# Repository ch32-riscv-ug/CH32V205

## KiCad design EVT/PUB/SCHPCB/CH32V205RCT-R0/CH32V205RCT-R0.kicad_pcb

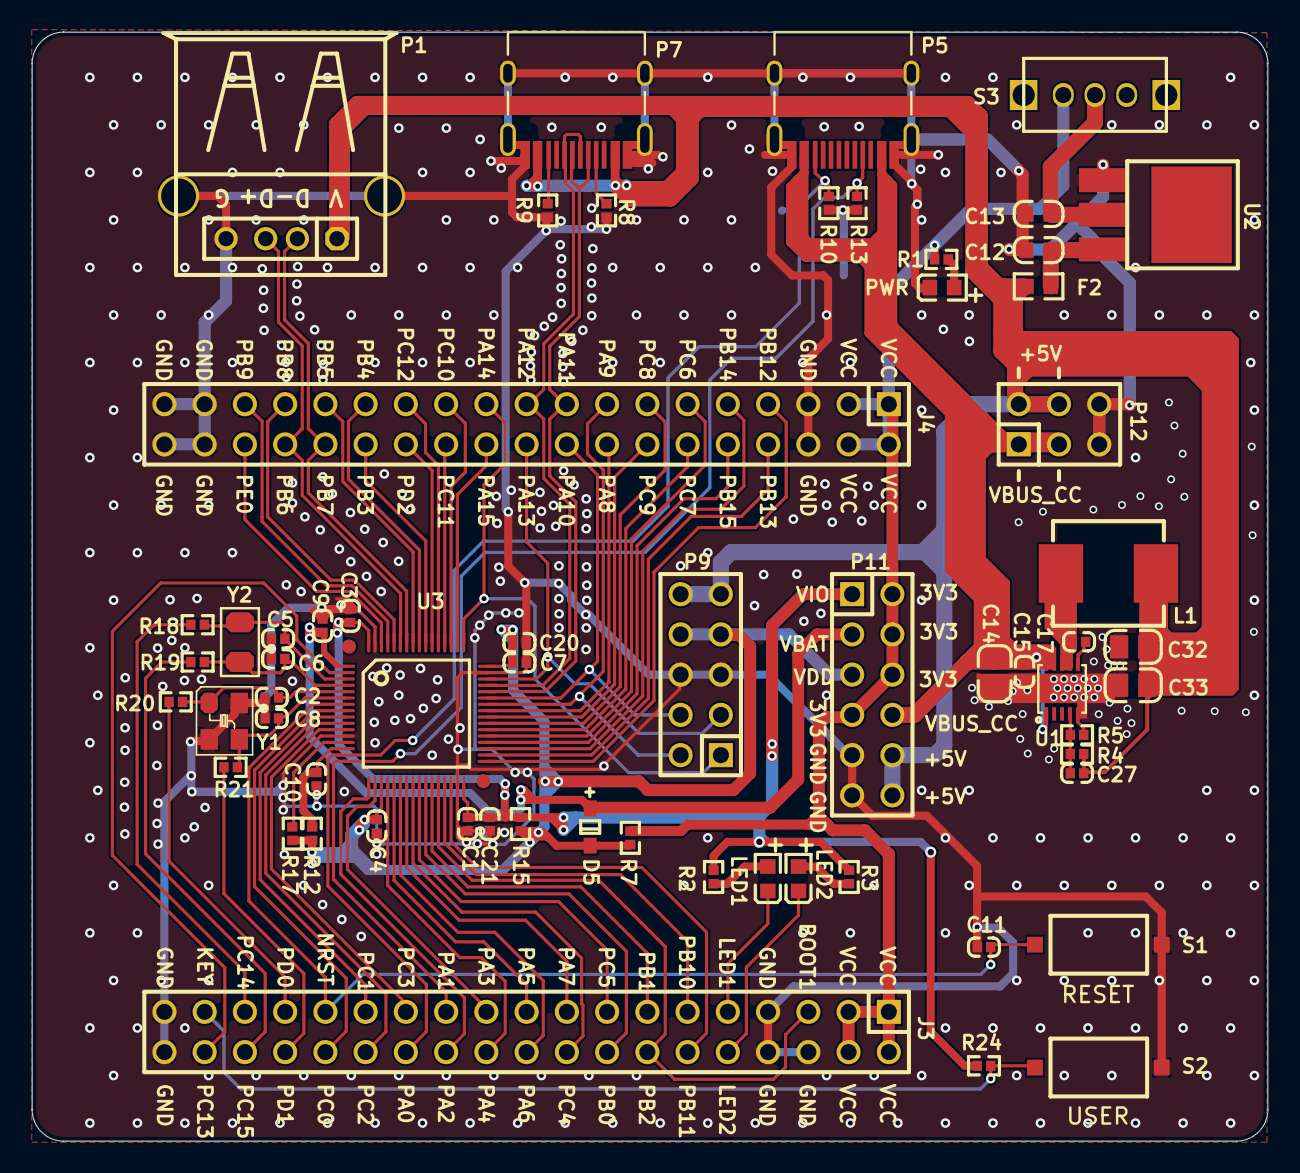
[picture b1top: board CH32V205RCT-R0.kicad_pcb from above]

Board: 2 copper layers, 78.0 x 70.0 mm, 61 parts (0 on the bottom side), 79 nets.

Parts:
C1, C3, C4, C7, C9, C10, C11: 0.1uF; 0402_C
C2, C8: 22pF; 0402_C
C5, C6: 12pF; 0402_C
C12, C13: 10uF; 0603_C
C14: NC(22uF/35V); 0805_C
C15: NC(0.1uF); 0402_C
C17: NC(100nF); 0402_C
C20, C21: 4.7uF; 0402_C
C27: NC(68pF); 0402_C
C32, C33: NC(22uF); 0805_C
D5: B0520WS; SOD-323
F2: 500mA; 0603
J3, J4: Header 19X2; IDC38-2.54mm
L1: NC(4.7uH/5A); IND-SMD_L7.0-W6.6
LED1: LED1 blue; 0603+
LED2: LED2 blue; 0603+
P1: USBHS; USBAF
P5: USBPD; TYPE-C-Receptacle-2.0
P7: TYPE-C; TYPE-C-Receptacle-2.0
P9: LINK; IDC10-2.54mm
P11: HEADER 6x2; IDC12-2.54mm
P12: HEADER 3x2; IDC6-2.54mm
PWR: POWER red; 0603+
R1, R2, R3: 1K; 0402
R4: NC(15K); 0402
R5: NC(4.7K); 0402
R7, R12, R15, R17: 0Ω; 0402
R8, R9, R10, R13: NC(5.1K); 0402
R18, R19, R20, R21: NC(0Ω); 0402
R24: 10K; 0402
S1: RESET; SMD_6.1x3.65x2.5mm-KEY
S2: USER; SMD_6.1x3.65x2.5mm-KEY
S3: SW; SW1
U1: NC(CH2024Q); DFN10_3X3
U2: 1117-3.3V; SOT-223
U3: CH32V205R; LQFP64_7X7
Y1: 8MHz; XT3225
Y2: 32.768k; FC-135

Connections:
3V3: J3.1, J3.2, J3.3, J3.4, J4.1, J4.2, J4.3, J4.4, P11.2, P11.4, P11.6, P11.7, R1.2, R7.1, S3.3
+5V: C27.1, C32.2, C33.2, F2.1, L1.2, P1.1, P7.A4, P7.B4, P9.9, P9.10, P11.10, P11.12, P12.2, P12.4, R4.2
BOOT1: J3.5, J3.14, U3.28
CC1: J3.26, P5.B5, R10.1, U3.15
CC2: J3.23, P5.A5, R13.1, U3.16
FB: C27.2, R4.1, R5.2, U1.4
GND: C1.1, C2.1, C3.1, C4.1, C5.2, C6.2, C7.1, C8.1, C9.2, C10.2, C11.1, C12.2, C13.2, C14.1, C15.1, C20.2, C21.1, C32.1, C33.1, J3.6, J3.7, J3.8, J3.37, J3.38, J4.5, J4.6, J4.35, J4.36, J4.37, J4.38, P1.0, P1.4, P5.0, P5.A1, P5.B1, P7.0, P7.A1, P7.B1, P9.5, P9.6, P11.9, P11.11, P12.5, P12.6, PWR.2, R5.1, R8.1, R9.1, R10.2, R13.2, S1.2, S2.2, U1.0, U1.5, U2.1, U3.12, U3.31, U3.47, U3.63, Y1.2, Y1.4
KEY: J3.35, R24.1, S2.1
LED1: J3.9, LED1.2
LED2: J3.10, LED2.2
NRST: C11.2, J3.29, S1.1, U3.7
NetC12_1: C12.1, F2.2, U2.3
NetC13_1: C13.1, S3.1, U2.2
NetC17_1: C17.1, U1.6
NetC17_2: C17.2, L1.1, U1.7, U1.8
NetLED1_1: LED1.1, R2.2
NetLED2_1: LED2.1, R3.2
NetP7_A5: P7.A5, R8.2
NetP7_B5: P7.B5, R9.2
NetPWR_1: PWR.1, R1.1
PA2: J3.24, U3.17
PA3: J3.21, U3.18
PA4: J3.22, U3.20
PA5: J3.19, U3.21
PA6: J3.20, U3.22
PA7: J3.17, U3.23
PA8: J4.16, U3.41
PA9: J4.15, P9.2, U3.42
PA10: J4.18, P9.4, U3.43
PA11: J4.17, P7.A7, P7.B7, U3.44
PA12: J4.19, P7.A6, P7.B6, U3.45
PA13: J4.20, P9.3, U3.46
PA14: J4.21, P9.1, U3.49
PA15: J4.22, U3.50
PB0: J3.16, U3.26
PB1: J3.13, U3.27
PB3: J4.28, U3.55
PB4: J4.27, U3.56
PB5: J4.29, U3.57
PB6: J4.32, P1.3, U3.59
PB7: J4.30, P1.2, U3.58
PB8: J4.31, U3.60
PB9: J4.33, U3.61
PB10: J3.11, U3.29
PB11: J3.12, U3.30
PB12: J4.7, U3.33
PB13: J4.8, U3.34
PB14: J4.9, U3.35
PB15: J4.10, U3.36
PC0: J3.30, U3.8
PC1: J3.27, U3.9
PC2: J3.28, U3.10
PC3: J3.25, U3.11
PC4: J3.18, U3.24
PC5: J3.15, U3.25
PC6: J4.11, U3.37
PC7: J4.12, U3.38
PC8: J4.13, U3.39
PC9: J4.14, U3.40
PC10: J4.23, U3.51
PC11: J4.24, U3.52
PC12: J4.25, U3.53
PC13: J3.36, U3.2
PC14: J3.33, R18.2
PC15: J3.34, R19.1
PD0: J3.31, R20.1
PD1: J3.32, R21.1
PD2: J4.26, U3.54
PE0: J4.34, U3.62
VBAT: C9.1, D5.1, P11.3, U3.1
VBUS_CC: C14.2, C15.2, P5.A4, P5.B4, P11.8, P12.1, P12.3, U1.1, U1.9, U1.10
VDD: C4.2, C7.2, C20.1, D5.2, P9.7, P9.8, P11.5, R7.2, R12.2, R15.2, R17.1, U3.19, U3.48
VDDA: C10.1, R12.1, U3.14
VIO: C1.2, C3.2, C21.2, P11.1, R2.1, R3.1, R15.1, R24.2, U3.32, U3.64
VREF+: R17.2, U3.13
X32KI: C5.1, R18.1, U3.3, Y2.1
X32KO: C6.1, R19.2, U3.4, Y2.2
XI: C2.2, R20.2, U3.5, Y1.1
XO: C8.2, R21.2, U3.6, Y1.3

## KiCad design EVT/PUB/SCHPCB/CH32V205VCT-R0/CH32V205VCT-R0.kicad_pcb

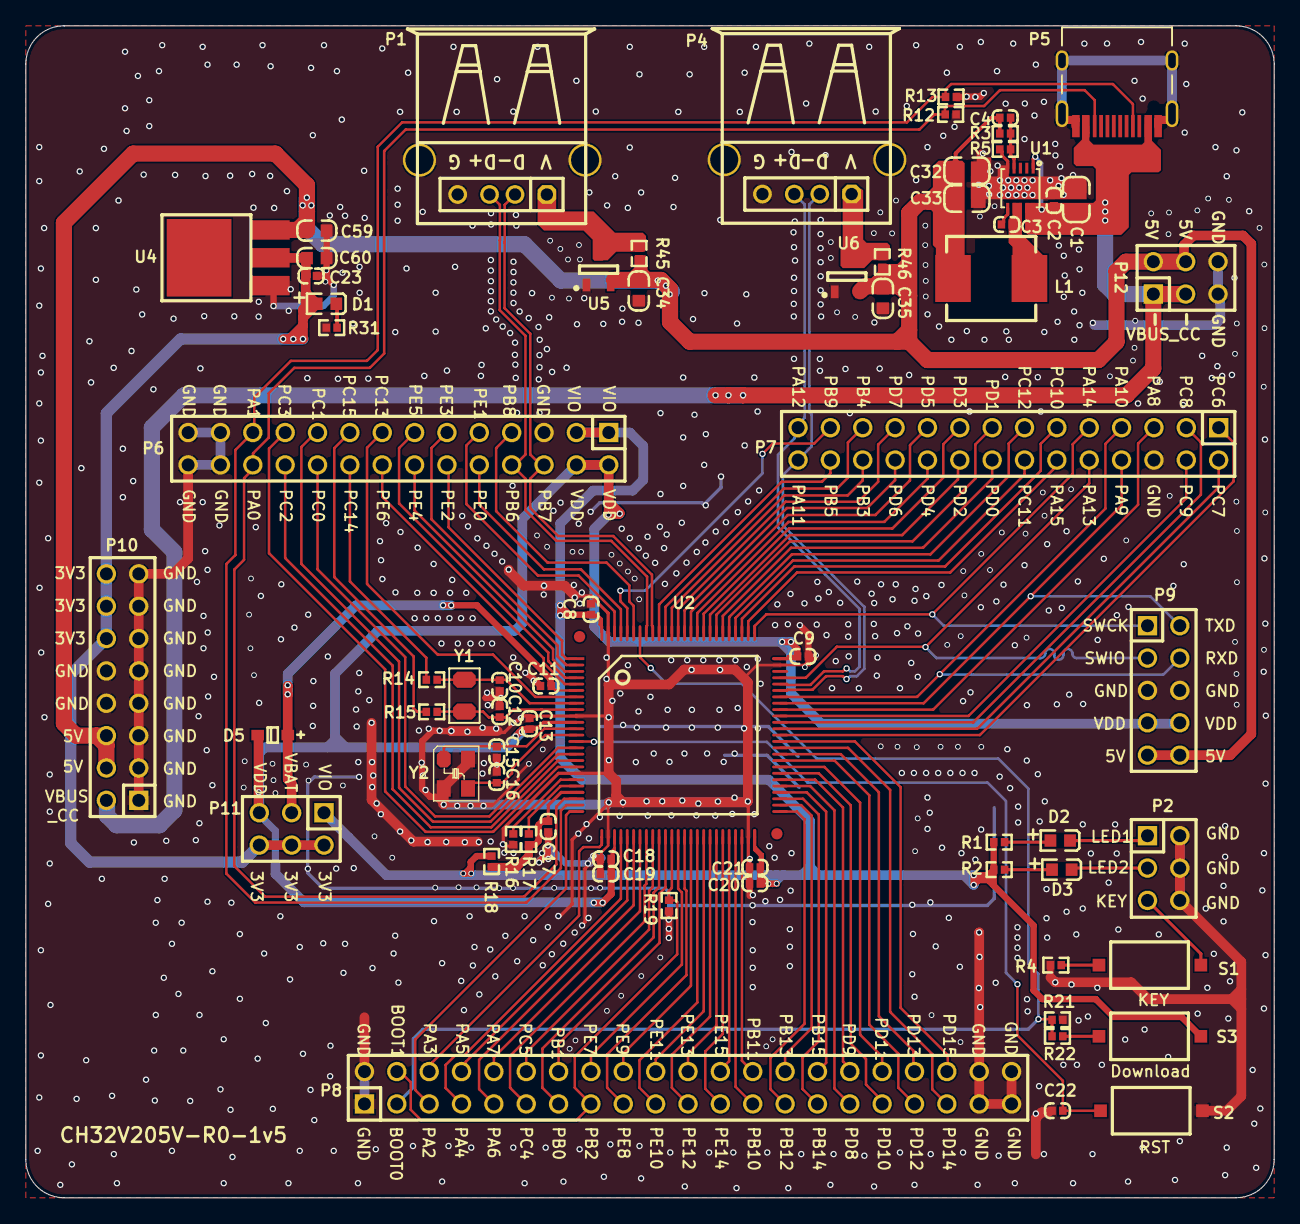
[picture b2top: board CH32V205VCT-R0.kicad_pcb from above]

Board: 2 copper layers, 98.0 x 92.0 mm, 69 parts (0 on the bottom side), 109 nets.

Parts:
C1: NC(22uF/35V); 0805_C
C2: NC(0.1uF); 0402_C
C3: NC(100nF); 0402_C
C4: NC(68pF); 0402_C
C8, C9, C11, C13, C17, C18, C21, C22, C23: 0.1uF; 0402_C
C10, C12: 12pF; 0402_C
C15, C16: 22pF; 0402_C
C19, C20: 4.7uF; 0402_C
C32, C33: NC(22uF); 0805_C
C34, C35, C59, C60: 10uF; 0603_C
D1, D3: RED; 0603+
D2: BLUE; 0603+
D5: B0520WS; SOD-323
L1: NC(4.7uH/5A); IND-SMD_L7.0-W6.6
P1: USBHS; USBAF
P2: IO; IDC6-2.54mm
P4: USBFS; USBAF
P5: USBPD; TYPE-C-Receptacle-2.0
P6, P7: IDC28-2.54MM
P8: HEADER 21x2; IDC42-2.54MM
P9: LINK; IDC10-2.54mm
P10: HEADER 8x2; IDC16-2.54mm
P11, P12: HEADER 3x2; IDC6-2.54mm
R1, R2, R22, R31: 1K; 0402
R3: NC(15K); 0402
R4, R19, R21: 10K; 0402
R5: NC(4.7K); 0402
R12, R13: NC(5.1K); 0402
R14, R15: NC(0R); 0402
R16, R17, R18: 0R; 0402
R45, R46: NC(0Ω); 0402
S1: KEY; SMD_6.1x3.65x2.5mm-KEY
S2: RST#; SMD_6.1x3.65x2.5mm-KEY
S3: Download; SMD_6.1x3.65x2.5mm-KEY
U1: NC(CH2024Q); DFN10_3X3
U2: CH32V205V; LQFP100
U4: 1117-3.3V; SOT-223
U5, U6: CH213; SOT-23-3
Y1: 32768Hz; FC-135
Y2: 8MHz; XT3225

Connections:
3V3: C23.1, C60.1, D1.1, P10.12, P10.14, P10.16, P11.2, P11.4, P11.6, U4.2
5V: C4.1, C32.2, C33.2, C34.1, C35.1, C59.1, L1.2, P9.9, P9.10, P10.4, P10.6, P12.2, P12.4, R3.2, R45.1, R46.1, U4.3, U5.2, U6.2
BOOT0: P8.3, R21.1, R22.1, U2.94
BOOT1: P8.4, P8.15, R19.1, U2.37
CC1: P5.B5, P6.24, R12.1, U2.23
CC2: P5.A5, P6.23, R13.1, U2.24
FB: C4.2, R3.1, R5.2, U1.4
GND: C1.1, C2.1, C8.1, C9.2, C10.1, C11.1, C12.1, C13.2, C15.1, C16.1, C17.2, C18.1, C19.2, C20.2, C21.2, C22.1, C23.2, C32.1, C33.1, C34.2, C35.2, C59.2, C60.2, P1.0, P1.4, P2.2, P2.4, P2.6, P4.0, P4.4, P5.0, P5.A1, P5.B1, P6.5, P6.25, P6.26, P6.27, P6.28, P7.6, P8.1, P8.2, P8.39, P8.40, P8.41, P8.42, P9.5, P9.6, P10.1, P10.3, P10.5, P10.7, P10.8, P10.9, P10.10, P10.11, P10.13, P10.15, P12.5, P12.6, R4.1, R5.1, R12.2, R13.2, R16.1, R19.2, R21.2, R31.1, S2.1, U1.0, U1.5, U2.10, U2.19, U2.27, U2.49, U2.74, U2.99, U4.1, U5.1, U6.1, Y2.2, Y2.4
KEY: P2.5, S1.1
LED1: D2.2, P2.1
LED2: D3.2, P2.3
NRST: C22.2, S2.2, U2.14
NetC3_1: C3.1, U1.6
NetC3_2: C3.2, L1.1, U1.7, U1.8
NetD1_2: D1.2, R31.2
NetD2_1: D2.1, R1.2
NetD3_1: D3.1, R2.2
NetR4_2: R4.2, S1.2
NetR22_2: R22.2, S3.2
PA2: P8.5, U2.25
PA3: P8.6, U2.26
PA4: P8.7, U2.29
PA5: P8.8, U2.30
PA6: P8.9, U2.31
PA7: P8.10, U2.32
PA8: P7.5, U2.67
PA9: P7.8, P9.2, U2.68
PA10: P7.7, P9.4, U2.69
PA11: P4.2, P7.28, U2.70
PA12: P4.3, P7.27, U2.71
PA13: P7.10, P9.3, U2.72
PA14: P7.9, P9.1, U2.76
PA15: P7.12, U2.77
PB0: P8.13, U2.35
PB1: P8.14, U2.36
PB3: P7.24, U2.89
PB4: P7.23, U2.90
PB5: P7.26, U2.91
PB6: P1.3, P6.8, U2.93
PB7: P1.2, P6.6, U2.92
PB8: P6.7, U2.95
PB9: P7.25, U2.96
PB10: P8.25, U2.47
PB11: P8.26, U2.48
PB12: P8.27, U2.51
PB13: P8.28, U2.52
PB14: P8.29, U2.53
PB15: P8.30, U2.54
PC0: P6.20, U2.15
PC1: P6.19, U2.16
PC2: P6.22, U2.17
PC3: P6.21, U2.18
PC4: P8.11, U2.33
PC5: P8.12, U2.34
PC6: P7.1, U2.63
PC7: P7.2, U2.64
PC8: P7.3, U2.65
PC9: P7.4, U2.66
PC10: P7.11, U2.78
PC11: P7.14, U2.79
PC12: P7.13, U2.80
PC13: P6.15, U2.7
PC14: P6.18, R14.1
PC15: P6.17, R15.1
PD0: P7.16, U2.81
PD1: P7.15, U2.82
PD2: P7.18, U2.83
PD3: P7.17, U2.84
PD4: P7.20, U2.85
PD5: P7.19, U2.86
PD6: P7.22, U2.87
PD7: P7.21, U2.88
PD8: P8.31, U2.55
PD9: P8.32, U2.56
PD10: P8.33, U2.57
PD11: P8.34, U2.58
PD12: P8.35, U2.59
PD13: P8.36, U2.60
PD14: P8.37, U2.61
PD15: P8.38, U2.62
PE0: P6.10, U2.97
PE1: P6.9, U2.98
PE2: P6.12, U2.1
PE3: P6.11, U2.2
PE4: P6.14, U2.3
PE5: P6.13, U2.4
PE6: P6.16, U2.5
PE7: P8.16, U2.38
PE8: P8.17, U2.39
PE9: P8.18, U2.40
PE10: P8.19, U2.41
PE11: P8.20, U2.42
PE12: P8.21, U2.43
PE13: P8.22, U2.44
PE14: P8.23, U2.45
PE15: P8.24, U2.46
VBAT: C11.2, D5.1, P11.3, U2.6
VBUS_CC: C1.2, C2.2, P5.A4, P5.B4, P10.2, P12.1, P12.3, U1.1, U1.9, U1.10
VBUS_FS: P4.1, R46.2, U6.3
VBUS_HS: P1.1, R45.2, U5.3
VDD: C9.1, C13.1, C18.2, C19.1, D5.2, P6.2, P6.4, P9.7, P9.8, P11.5, U2.11, U2.28, U2.75
VDDA: C17.1, R17.1, R18.2, U2.22
VIO: C8.2, C20.1, C21.1, P6.1, P6.3, P11.1, R1.1, R2.1, R18.1, S3.1, U2.50, U2.100
VREF+: R17.2, U2.21
VREF-: R16.2, U2.20
X32KI: C10.2, R14.2, U2.8, Y1.1
X32KO: C12.2, R15.2, U2.9, Y1.2
XI: C15.2, U2.12, Y2.1
XO: C16.2, U2.13, Y2.3

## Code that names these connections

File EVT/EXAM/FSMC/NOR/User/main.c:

/********************************** (C) COPYRIGHT *******************************
 * File Name          : main.c
 * Author             : WCH
 * Version            : V1.0.1
 * Date               : 2026/10/14
 * Description        : Main program body.
 *********************************************************************************
 * Copyright (c) 2021 Nanjing Qinheng Microelectronics Co., Ltd.
 * Attention: This software (modified or not) and binary are used for 
 * microcontroller manufactured by Nanjing Qinheng Microelectronics.
 *******************************************************************************/

/*
 *@Note
   This example is used to demonstrate the FSMC interface operating NorFlash-MT28EW128ABA1LJS-0SIT.
  PIN:
   (Latches)
    FSMC_NADV     -    PB7
    FSMC_NOE      -    PD4  (OE)
    FSMC_NWE      -    PD5  (WE)
    FSMC_NWAIT    -    PD6  (RY/BY#)
    FSMC_NE1      -    PD7  (CE)
    FSMC_D/A0     -    PD14
    FSMC_D/A1     -    PD15
    FSMC_D/A2     -    PD0
    FSMC_D/A3     -    PD1
    FSMC_D/A4     -    PE7
    FSMC_D/A5     -    PE8
    FSMC_D/A6     -    PE9
    FSMC_D/A7     -    PE10
    FSMC_D/A8     -    PE11
    FSMC_D/A9     -    PE12
    FSMC_D/A10    -    PE13
    FSMC_D/A11    -    PE14
    FSMC_D/A12    -    PE15
    FSMC_D/A13    -    PD8
    FSMC_D/A14    -    PD9
    FSMC_D/A15    -    PD10
    FSMC_A16      -    PD11
    FSMC_A17      -    PD12
    FSMC_A18      -    PD13
    FSMC_A19      -    PE3
    FSMC_A20      -    PE4
    FSMC_A21      -    PE5
    FSMC_A22      -    PE6

  The address line and data line of this routine are multiplexed
  and need to use a latch.
*/

#include "debug.h"
#include "FSMC_NOR.h"
/* Global define */
uint16_t TxBuffer[BUFFER_SIZE];
uint16_t RxBuffer[BUFFER_SIZE];
uint32_t WriteReadStatus = 0, Index = 0;
NOR_IDTypeDef NOR_ID;
/* Global Variable */


/*********************************************************************
 * @fn      main
 *
 * @brief   Main program.
 *
 * @return  none
 */
int main(void)
{
    SystemCoreClockUpdate();
    Delay_Init();
    USART_Printf_Init(115200);
    printf ("SystemCoreClk:%lu\r\n", (unsigned long)SystemCoreClock);
    printf("ChipID:%08x\r\n", DBGMCU_GetCHIPID() );
    printf("NorFlash TEST\n");

    FSMC_NorFlash_Init();
    NOR_ReadID(&NOR_ID);
    NOR_ReturnToReadMode();
    NOR_EraseBlock(WRITE_READ_ADDR);
    Fill_Buffer(TxBuffer, BUFFER_SIZE, 0x01);
    NOR_WriteBuffer(TxBuffer, WRITE_READ_ADDR, BUFFER_SIZE);
    NOR_ReadBuffer(RxBuffer, WRITE_READ_ADDR, BUFFER_SIZE);
    for (Index = 0x00; (Index < BUFFER_SIZE) && (WriteReadStatus == 0); Index++)
    {
        if (RxBuffer[Index] != TxBuffer[Index])
        {
            WriteReadStatus = Index + 1;
            printf("RxBuffer[%d]=%x\r\n",Index,RxBuffer[Index]);
            printf("TxBuffer[%d]=%x\r\n",Index,TxBuffer[Index]);
        }
    }
    if (WriteReadStatus == 0)
    {
        /* OK */
        printf("sucess\r\n");
    }
    else
    {
        /* KO */
        printf("error\r\n");
    }
    while(1);
}

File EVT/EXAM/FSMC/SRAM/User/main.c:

/********************************** (C) COPYRIGHT *******************************
 * File Name          : main.c
 * Author             : WCH
 * Version            : V1.0.1
 * Date               : 2026/10/14
 * Description        : Main program body.
 *********************************************************************************
 * Copyright (c) 2021 Nanjing Qinheng Microelectronics Co., Ltd.
 * Attention: This software (modified or not) and binary are used for 
 * microcontroller manufactured by Nanjing Qinheng Microelectronics.
 *******************************************************************************/

/*
 *@Note
   FSMC routine to operate NOR_ SRAM:
      This routine demonstrates the operation of IS62WV25616BLL model
      NOR_SRAM erase-read through FSMC interface.
  PIN:
    FSMC_NADV   -    PB7
    FSMC_NE1    -    PD7 (CS1)
    FSMC_NOE    -    PD4  (OE)
    FSMC_NWE    -    PD5  (WE)
    FSMC_NBL1   -    PE1  (UB)
    FSMC_NBL0   -    PE0  (LB)
    FSMC_D0     -    PD14
    FSMC_D1     -    PD15
    FSMC_D2     -    PD0
    FSMC_D3     -    PD1
    FSMC_D4     -    PE7
    FSMC_D5     -    PE8
    FSMC_D6     -    PE9
    FSMC_D7     -    PE10
    FSMC_D8     -    PE11
    FSMC_D9     -    PE12
    FSMC_D10    -    PE13
    FSMC_D11    -    PE14
    FSMC_D12    -    PE15
    FSMC_D13    -    PD8
    FSMC_D14    -    PD9
    FSMC_D15    -    PD10
    FSMC_A16    -    PD11
    FSMC_A17    -    PD12

  The address line and data line of this routine are multiplexed
  and need to use a latch.
*/

#include "debug.h"

/* Global define */
#define Bank1_SRAM1_ADDR    ((u32)(0x60000000))
/* Global Variable */
/*********************************************************************
 * @fn      FSMC_SRAM_Init
 *
 * @brief   Init FSMC
 *
 * @return  none
 */
void FSMC_SRAM_Init(void)
{
    FSMC_NORSRAMInitTypeDef  FSMC_NORSRAMInitStructure={0};
    FSMC_NORSRAMTimingInitTypeDef  readWriteTiming={0};
    GPIO_InitTypeDef  GPIO_InitStructure={0};

    RCC_PB2PeriphClockCmd(RCC_PB2Periph_GPIOB | RCC_PB2Periph_GPIOD | RCC_PB2Periph_GPIOE|RCC_PB2Periph_AFIO,ENABLE);
    RCC_HBPeriphClockCmd(RCC_HBPeriph_FSMC,ENABLE);
    /* FSMC_NADV */
    GPIO_InitStructure.GPIO_Pin = GPIO_Pin_7;
    GPIO_InitStructure.GPIO_Mode = GPIO_Mode_AF_PP;
    GPIO_InitStructure.GPIO_Speed = GPIO_Speed_High;
    GPIO_Init(GPIOB, &GPIO_InitStructure);
    GPIO_PinAFConfig(GPIOB, GPIO_PinSource7, GPIO_AF6);

    GPIO_InitStructure.GPIO_Pin = GPIO_Pin_0|GPIO_Pin_1|GPIO_Pin_4|GPIO_Pin_5|GPIO_Pin_7|GPIO_Pin_8|GPIO_Pin_9|GPIO_Pin_10|GPIO_Pin_11|GPIO_Pin_12|GPIO_Pin_14|GPIO_Pin_15;
    GPIO_InitStructure.GPIO_Mode = GPIO_Mode_AF_PP;
    GPIO_InitStructure.GPIO_Speed = GPIO_Speed_High;
    GPIO_Init(GPIOD, &GPIO_InitStructure);
    GPIO_PinAFConfig(GPIOD, GPIO_PinSource0, GPIO_AF7);
    GPIO_PinAFConfig(GPIOD, GPIO_PinSource1, GPIO_AF7);
    GPIO_PinAFConfig(GPIOD, GPIO_PinSource4, GPIO_AF7);
    GPIO_PinAFConfig(GPIOD, GPIO_PinSource5, GPIO_AF7);   
    GPIO_PinAFConfig(GPIOD, GPIO_PinSource7, GPIO_AF7); 
    GPIO_PinAFConfig(GPIOD, GPIO_PinSource8, GPIO_AF7);
    GPIO_PinAFConfig(GPIOD, GPIO_PinSource9, GPIO_AF7);
    GPIO_PinAFConfig(GPIOD, GPIO_PinSource10, GPIO_AF7);
    GPIO_PinAFConfig(GPIOD, GPIO_PinSource11, GPIO_AF7);
    GPIO_PinAFConfig(GPIOD, GPIO_PinSource12, GPIO_AF7);
    GPIO_PinAFConfig(GPIOD, GPIO_PinSource14, GPIO_AF7);
    GPIO_PinAFConfig(GPIOD, GPIO_PinSource15, GPIO_AF7);

    GPIO_InitStructure.GPIO_Pin = GPIO_Pin_0|GPIO_Pin_1|GPIO_Pin_7|GPIO_Pin_8|GPIO_Pin_9|GPIO_Pin_10|GPIO_Pin_11|GPIO_Pin_12|GPIO_Pin_13|GPIO_Pin_14|GPIO_Pin_15;
    GPIO_InitStructure.GPIO_Mode = GPIO_Mode_AF_PP;
    GPIO_InitStructure.GPIO_Speed = GPIO_Speed_High;
    GPIO_Init(GPIOE, &GPIO_InitStructure);
    GPIO_PinAFConfig(GPIOE, GPIO_PinSource0, GPIO_AF7);
    GPIO_PinAFConfig(GPIOE, GPIO_PinSource1, GPIO_AF7);
    GPIO_PinAFConfig(GPIOE, GPIO_PinSource7, GPIO_AF7);
    GPIO_PinAFConfig(GPIOE, GPIO_PinSource8, GPIO_AF7);
    GPIO_PinAFConfig(GPIOE, GPIO_PinSource9, GPIO_AF7);
    GPIO_PinAFConfig(GPIOE, GPIO_PinSource10, GPIO_AF7);
    GPIO_PinAFConfig(GPIOE, GPIO_PinSource11, GPIO_AF7);
    GPIO_PinAFConfig(GPIOE, GPIO_PinSource12, GPIO_AF7);
    GPIO_PinAFConfig(GPIOE, GPIO_PinSource13, GPIO_AF7);
    GPIO_PinAFConfig(GPIOE, GPIO_PinSource14, GPIO_AF7);
    GPIO_PinAFConfig(GPIOE, GPIO_PinSource15, GPIO_AF7);

    readWriteTiming.FSMC_AddressSetupTime = 0x00;
    readWriteTiming.FSMC_AddressHoldTime = 0x00;
    readWriteTiming.FSMC_DataSetupTime = 0x03;
    readWriteTiming.FSMC_BusTurnAroundDuration = 0x00;
    readWriteTiming.FSMC_AccessMode = FSMC_AccessMode_A;

    FSMC_NORSRAMInitStructure.FSMC_Bank = FSMC_Bank1_NORSRAM1;
    FSMC_NORSRAMInitStructure.FSMC_DataAddressMux = FSMC_DataAddressMux_Enable;
    FSMC_NORSRAMInitStructure.FSMC_MemoryType =FSMC_MemoryType_SRAM;
    FSMC_NORSRAMInitStructure.FSMC_MemoryDataWidth = FSMC_MemoryDataWidth_16b;
    FSMC_NORSRAMInitStructure.FSMC_BurstAccessMode =FSMC_BurstAccessMode_Disable;
    FSMC_NORSRAMInitStructure.FSMC_WaitSignalPolarity = FSMC_WaitSignalPolarity_Low;
    FSMC_NORSRAMInitStructure.FSMC_AsynchronousWait=FSMC_AsynchronousWait_Disable;
    FSMC_NORSRAMInitStructure.FSMC_WaitSignalActive = FSMC_WaitSignalActive_BeforeWaitState;
    FSMC_NORSRAMInitStructure.FSMC_WriteOperation = FSMC_WriteOperation_Enable;
    FSMC_NORSRAMInitStructure.FSMC_WaitSignal = FSMC_WaitSignal_Disable;
    FSMC_NORSRAMInitStructure.FSMC_ExtendedMode = FSMC_ExtendedMode_Disable;
    FSMC_NORSRAMInitStructure.FSMC_WriteBurst = FSMC_WriteBurst_Disable;
    FSMC_NORSRAMInitStructure.FSMC_ReadWriteTimingStruct = &readWriteTiming;
    FSMC_NORSRAMInitStructure.FSMC_WriteTimingStruct = &readWriteTiming;

    FSMC_NORSRAMInit(&FSMC_NORSRAMInitStructure);
    FSMC_NORSRAMCmd(FSMC_Bank1_NORSRAM1, ENABLE);
}



/*********************************************************************
 * @fn      main
 *
 * @brief   Main program.
 *
 * @return  none
 */
int main(void)
{
    u32 i=0;
    SystemCoreClockUpdate();
    Delay_Init();
    USART_Printf_Init(115200);
    printf ("SystemCoreClk:%lu\r\n", (unsigned long)SystemCoreClock);
    printf("ChipID:%08x\r\n", DBGMCU_GetCHIPID() );
    printf("SRAM TEST\r\n");

	FSMC_SRAM_Init();

	printf("Write data:\n");
	for(i=0; i<1024; i++){
      *(u32*)(Bank1_SRAM1_ADDR + 4*i) = i;
	}

	printf("Read data:\n");
	for(i=0; i<1024; i++){
      printf("%08x ", *(u32*)(Bank1_SRAM1_ADDR + 4*i));
    } printf("\n");

	while(1);
}

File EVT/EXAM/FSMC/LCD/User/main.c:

/********************************** (C) COPYRIGHT *******************************
 * File Name          : main.c
 * Author             : WCH
 * Version            : V1.0.1
 * Date               : 2026/10/14
 * Description        : Main program body.
 *********************************************************************************
 * Copyright (c) 2021 Nanjing Qinheng Microelectronics Co., Ltd.
 * Attention: This software (modified or not) and binary are used for 
 * microcontroller manufactured by Nanjing Qinheng Microelectronics.
 *******************************************************************************/

/*
 *@Note
   FSMC routine to operate TFTLCD:
  LCD--PIN:
    PD11--FSMC_A16
    PD12--FSMC_A17
    PD5 --FSMC_NEW
    PD4 --FSMC_NOE
    PA15--LCDRST#
    PD14--FSMC_D0
    PD15--FSMC_D1
    PD0 --FSMC_D2
    PD1--FSMC_D3
    PE7--FSMC_D4
    PE8 --FSMC_D5
    PE9 --FSMC_D6
    PE10--FSMC_D7
    PE11--FSMC_D8
    PE12--FSMC_D9
    PE13--FSMC_D10
    PE14--FSMC_D11
    PE15--FSMC_D12
    PD8 --FSMC_D13
    PD9--FSMC_D14
    PD10--FSMC_D15
    PB14--IO_BLCTR
*/


#include "debug.h"
#include "lcd.h"
/* Global define */

/* Global Variable */

/*********************************************************************
 * @fn      LCD_Reset_GPIO_Init
 *
 * @brief   Init LCD reset GPIO.
 *
 * @return  none
 */
void LCD_Reset_GPIO_Init(void)
{
    GPIO_InitTypeDef  GPIO_InitStructure={0};

    RCC_PB2PeriphClockCmd(RCC_PB2Periph_GPIOA, ENABLE);
    GPIO_InitStructure.GPIO_Pin = GPIO_Pin_15;
    GPIO_InitStructure.GPIO_Mode = GPIO_Mode_Out_PP;
    GPIO_InitStructure.GPIO_Speed = GPIO_Speed_High;
    GPIO_Init(GPIOA, &GPIO_InitStructure);
    GPIO_SetBits(GPIOA,GPIO_Pin_15);
}


/*********************************************************************
 * @fn      main
 *
 * @brief   Main program.
 *
 * @return  none
 */
int main(void)
{
	u8 x=0;
	LCD_Reset_GPIO_Init();
	//LCD reset
	GPIO_ResetBits(GPIOA,GPIO_Pin_15);
	Delay_Ms(100);
	GPIO_SetBits(GPIOA,GPIO_Pin_15);

    LCD_Init();
	POINT_COLOR=RED;		
	 
    while(1) 
	{		 
		switch(x)
		{
			case 0:LCD_Clear(WHITE);break;
			case 1:LCD_Clear(BLACK);break;
			case 2:LCD_Clear(BLUE);break;
			case 3:LCD_Clear(RED);break;
			case 4:LCD_Clear(MAGENTA);break;
			case 5:LCD_Clear(GREEN);break;
			case 6:LCD_Clear(CYAN);break;
			case 7:LCD_Clear(YELLOW);break;
			case 8:LCD_Clear(BRRED);break;
			case 9:LCD_Clear(GRAY);break;
			case 10:LCD_Clear(LGRAY);break;
			case 11:LCD_Clear(BROWN);break;
            default:break;
		}
		POINT_COLOR=RED;	  
		LCD_ShowString(30,40,210,24,24,"CH32V205");
        Delay_Ms(5);
		LCD_ShowString(30,70,200,16,16,"TFTLCD TEST");
        Delay_Ms(5);
		LCD_ShowString(30,90,200,16,16,"WCH");
        Delay_Ms(5);
	    x++;
		if(x==12)x=0;			   		 
		Delay_Ms(1000);	

	} 
}

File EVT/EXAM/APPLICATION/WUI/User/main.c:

/********************************** (C) COPYRIGHT *******************************
 * File Name          : main.c
 * Author             : WCH
 * Version            : V1.0.0
 * Date               : 2026/08/12
 * Description        : Main program body.
 *********************************************************************************
 * Copyright (c) 2023 Nanjing Qinheng Microelectronics Co., Ltd.
 * Attention: This software (modified or not) and binary are used for
 * microcontroller manufactured by Nanjing Qinheng Microelectronics.
 *******************************************************************************/

/*
 *@Note
 A demo for wui
  pins: 
    FLASH_CS   -- PA4
    FLASH_DO   -- PA6
    FLASH_DI   -- PA7
    FLASH_CLK  -- PA5
    
    QSPI_SCK   -- PB2
    QSPI_SIOX0 -- PB8
    LCD_RST    -- PC13
    QSPI_SIOX1 -- PB9
    QSPI_CSX   -- PB1
    BL_EN      -- PB3
    QSPI_SIOX2 -- PB10
    QSPI_SIOX3 -- PB11
    IIC_SDA    -- PB7
    IIC_SCL    -- PB6
    TR_RST     -- PB14
    TR_INT     -- PB15
 */

#include "debug.h"
#include "string.h"
#include "ch32v205_qspi.h"
#include "wui.h"
#include "wui_user/wui_page.h"
#include "touch.h"
#include "wui_port.h"
/* Global define */

/* Global Variable */

static uint8_t wui_heap_buffer[4 * 1024];
#define TIM_PCK (8000ul)
// WUIconfig init
static const wui_init_data_t wui_init_data = {
    .page_count = WUI_PAGE_COUNT,
    .width = LCD_WIDTH,
    .height = LCD_HEIGHT,
    .heap_addr = wui_heap_buffer,
    .heap_size = sizeof (wui_heap_buffer),
};

/*********************************************************************
 * @fn      TIM4_init
 *
 * @brief   Initialize TIM4 for WCHGUI
 *        
 * @return  none.
 */

void TIM4_init() {
    RCC_PB1PeriphClockCmd (RCC_PB1Periph_TIM4, ENABLE);

    TIM_TimeBaseInitTypeDef TIM_TimeBaseInitStructure = {0};

    TIM_Cmd (TIM4, DISABLE);

    TIM_TimeBaseInitStructure.TIM_Period = 0xffff;
    TIM_TimeBaseInitStructure.TIM_Prescaler = ((SystemCoreClock) / TIM_PCK) - 1;
    TIM_TimeBaseInitStructure.TIM_ClockDivision = TIM_CKD_DIV1;
    TIM_TimeBaseInitStructure.TIM_CounterMode = TIM_CounterMode_Up;
    TIM_TimeBaseInit (TIM4, &TIM_TimeBaseInitStructure);

    TIM_ARRPreloadConfig (TIM4, DISABLE);
    TIM_ClearFlag (TIM4, TIM_FLAG_Update);

    TIM_Cmd (TIM4, ENABLE);
}

/*********************************************************************
 * @fn      TIM3_Encoder_Init
 *
 * @brief   Initialize TIM3 for encoder
 *        
 * @return  none.
 */
void TIM3_Encoder_Init() {
    TIM_TimeBaseInitTypeDef TIM_TimeBaseStructure = {0};
    TIM_ICInitTypeDef TIM_ICInitStructure = {0};
    GPIO_InitTypeDef GPIO_InitStructure = {0};

    RCC_PB2PeriphClockCmd (RCC_PB2Periph_GPIOA, ENABLE);
    RCC_PB1PeriphClockCmd (RCC_PB1Periph_TIM3, ENABLE);
    RCC_PB2PeriphClockCmd (RCC_PB2Periph_AFIO, ENABLE);
    RCC_PB2PeriphClockCmd (RCC_PB2Periph_GPIOB, ENABLE);

    GPIO_PinAFConfig (GPIOB, GPIO_PinSource5, GPIO_AF1);
    GPIO_PinAFConfig (GPIOB, GPIO_PinSource4, GPIO_AF1);
    GPIO_InitStructure.GPIO_Pin = GPIO_Pin_4 | GPIO_Pin_5;
    GPIO_InitStructure.GPIO_Mode = GPIO_Mode_IN_FLOATING;
    GPIO_Init (GPIOB, &GPIO_InitStructure);

    TIM_TimeBaseStructInit (&TIM_TimeBaseStructure);
    TIM_TimeBaseStructure.TIM_Prescaler = 0x0;
    TIM_TimeBaseStructure.TIM_Period = 160;
    TIM_TimeBaseStructure.TIM_ClockDivision = TIM_CKD_DIV1;
    TIM_TimeBaseStructure.TIM_CounterMode = TIM_CounterMode_Up;
    TIM_TimeBaseInit (TIM3, &TIM_TimeBaseStructure);

    TIM_EncoderInterfaceConfig (TIM3, TIM_EncoderMode_TI12, TIM_ICPolarity_Rising, TIM_ICPolarity_Rising);

    TIM_ICStructInit (&TIM_ICInitStructure);
    TIM_ICInitStructure.TIM_ICFilter = 10;
    TIM_ICInit (TIM3, &TIM_ICInitStructure);

    TIM_SetCounter (TIM3, 0);
    TIM_Cmd (TIM3, ENABLE);
}

/*********************************************************************
 * @fn      check_direction
 *
 * @brief    Compute the absolute value of a signed 32-bit integer.
 *
 * @param   a Signed 32-bit integer.
 *
 * @return  Absolute value of a
 */
uint32_t static inline iabs (int32_t a) {
    if (a < 0) {
        return -a;
    }
    return a;
}

/*********************************************************************
 * @fn      check_direction
 *
 * @brief   Detect the rotation direction of the encoder
 *
 * @param   current_value The current count value
 *
 * @return  direction The direction of the encoder's rotation
 */
int32_t check_direction (int current_value) {

    static int last_value = 0;

    if (current_value == last_value) {
        return 0;
    }

    int diff = current_value - last_value;
    if (iabs (diff) < 4) {
        return 0;
    }

    int32_t direction;

    if (iabs (diff) < 80) {
        if (diff > 0) {
            direction = 1;
        } else {
            direction = -1;
        }
    } else {
        if (diff > 0) {
            direction = -1;
        } else {
            direction = 1;
        }
    }

    last_value = current_value;
    return direction;
}

#define ENC_KEY_PORT GPIOA
#define ENC_KEY_PIN (GPIO_Pin_3)

#define ENC_KEY() ((ENC_KEY_PORT->INDR & ENC_KEY_PIN) == 0)

uint32_t key3_state = 0;

/*********************************************************************
 * @fn      Key_GPIOInit
 *
 * @brief   Initialization of the key pins of the encoder
 *
 * @return  none.
 */
void Key_GPIOInit (void) {

    GPIO_InitTypeDef GPIO_InitStructure = {0};

    GPIO_InitStructure.GPIO_Pin = ENC_KEY_PIN;
    GPIO_InitStructure.GPIO_Mode = GPIO_Mode_IPU;
    GPIO_Init (ENC_KEY_PORT, &GPIO_InitStructure);
}

/*********************************************************************
 * @fn      main
 *
 * @brief   Main program.
 *
 * @return  none
 */
int main (void) {

    SystemCoreClockUpdate();
    Delay_Init();
    USART_Printf_Init (2000000);
    printf ("SystemClk:%d\r\n", SystemCoreClock);
    printf (__TIME__ "\n");

    SPI_FLASH_Init();

    uint32_t id = SPI_Flash_ReadJedecDeviceID();
    printf ("flash_id %x\n", id);

    QSPI_LCD_Init();
    TIM3_Encoder_Init();
    TIM4_init();
    Key_GPIOInit();

    LCD_DrawColor_Quad (0, 0, 360, 360, 0x0);
    Touch_Init();

    wui_init ((wui_init_data_t *)&wui_init_data);

    wui_register_hal (wui_get_hal());

    wui_page_switch (WUI_START_PAGE);

    while (1) {
        uint16_t now = TIM4->CNT;
        if (now > 16) {
            now = now / 8;
            TIM4->CNT = 0;
            wui_page_ui_tick (now);
        }
        wui_page_ui_update();
        uint32_t tcnt = TIM3->CNT;

        int32_t dir = check_direction (tcnt);

        if (dir > 0) {
            HW_Key_event ('a');
        } else if (dir < 0) {
            HW_Key_event ('d');
        }

        uint32_t k3 = ENC_KEY();
        if (k3) {
            if (key3_state) {
            } else {
                key3_state = 1;
                HW_Key_event ('b');
            }
        } else {
            key3_state = 0;
        }
    }
}

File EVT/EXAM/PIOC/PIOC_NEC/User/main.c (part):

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
/* PIOC IO 0/1 pin select definition */
#define	PIOC_IO0_1	1 //PA11(AF4)
#define PIOC_IO0_2  2 //PB10(AF4) 
#define PIOC_IO0_3  3 //PD3(AF4)
#define PIOC_IO0_4  4 //PE3(AF4)

#define PIOC_IO1_1	5 //PA12(AF4)
#define PIOC_IO1_2	6 //PB11(AF4)
#define PIOC_IO1_3	7 //PD4(AF4)
#define PIOC_IO1_4	8 //PE4(AF4)

#define  PIOC_IO    PIOC_IO0_1
/*********************************************************************
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 *
 * @brief   Initializes PIOC NEC remote.
 *
 * @param   mod - 0:receive pin PC18 or PC7
 *                1:receive pin PC19
 *
 * @return  none
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
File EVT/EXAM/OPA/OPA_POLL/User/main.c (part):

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 *@Note
 *OPA positive input polling function:
 *
 *OPA1_CHN0--PB11
 *OPA1_OUT--PA3
 *P0-PB5 P1-PB0  P2-PB12
 *The number of positive terminals polling is 3. The polling time is 1000ms, and the corresponding 
 *channel can be queried when the output is high voltage. OPA can be selected as the brake signal,
 *and the brake is effective when the output is high.
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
